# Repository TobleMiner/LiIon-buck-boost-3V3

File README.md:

Single Cell LiIon to 3.3 V buck/boost converter
===============================================

This board is a small breakout board for the TI TPS63030 designed to convert
any input voltage from up to 5.5 V down to 1.8 V to 3.3 V @ 500 mA.

The board is designed to be both small and fit a standard breadboard.

# PCB

## Top

## Bottom

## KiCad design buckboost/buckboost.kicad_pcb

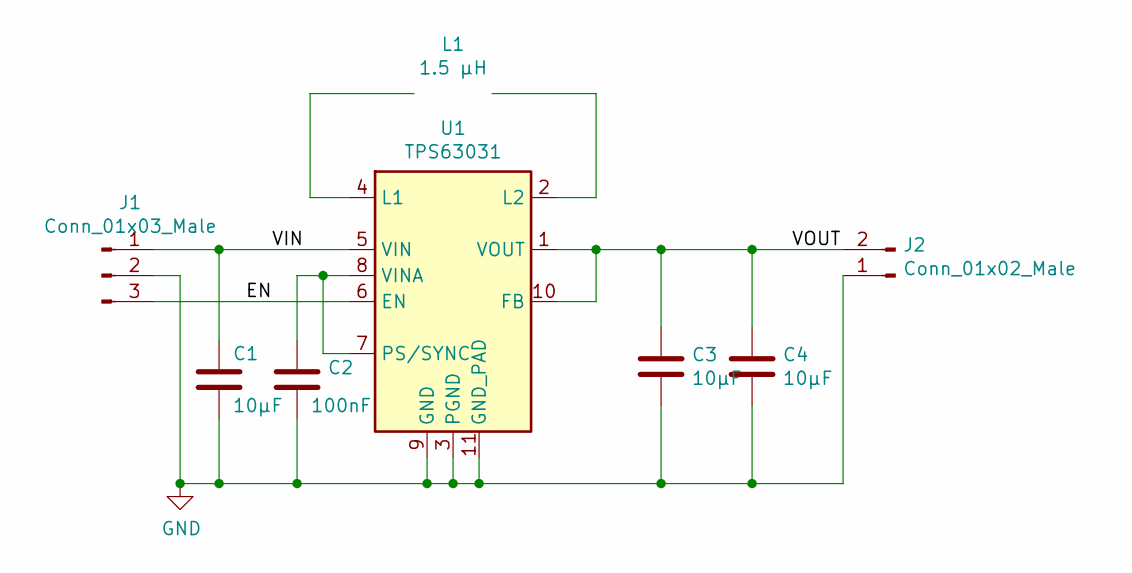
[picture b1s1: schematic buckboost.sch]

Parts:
C1, C3, C4: 10µF; C_0805_2012Metric
C2: 100nF; C_0805_2012Metric
J1: Conn_01x03_Male; PinHeader_1x03_P2.54mm_Vertical
J2: Conn_01x02_Male; PinHeader_1x02_P2.54mm_Vertical
L1: 1.5 µH; L_1210_3225Metri
U1: TPS63031; Texas_DRC0010J_ThermalVias.3

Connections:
/EN: J1.3, U1.6 (EN)
/VIN: C1.1, J1.1, U1.5 (VIN)
/VOUT: C3.1, C4.1, J2.2, U1.1 (VOUT), U1.10 (FB)
GND: C1.2, C2.2, C3.2, C4.2, J1.2, J2.1, U1.3 (PGND), U1.9 (GND), U1.11 (GND_PAD)
unnamed: C2.1, U1.7 (PS/SYNC), U1.8 (VINA)
unnamed: L1.1, U1.4 (L1)
unnamed: L1.2, U1.2 (L2)

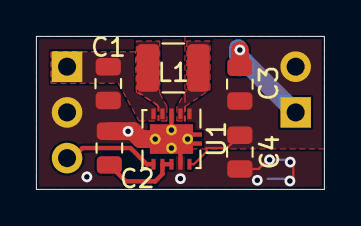
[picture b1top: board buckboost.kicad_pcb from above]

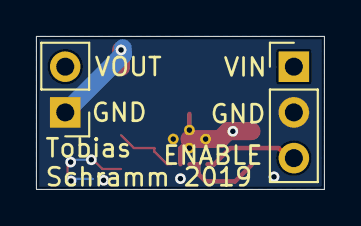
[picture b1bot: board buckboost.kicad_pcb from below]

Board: 2 copper layers, 16.0 x 8.5 mm, 8 parts (2 on the bottom side), 7 nets.

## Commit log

2019-04-26 Move measurements to Eco1.User layer
2019-04-26 Move silkscreen designators away from board outline
2019-04-26 Add Readme
2019-04-26 Add LICENSE
2019-04-26 Display images inline
2019-04-26 Add inductor value
2019-04-28 Update LICENSE to 2019
